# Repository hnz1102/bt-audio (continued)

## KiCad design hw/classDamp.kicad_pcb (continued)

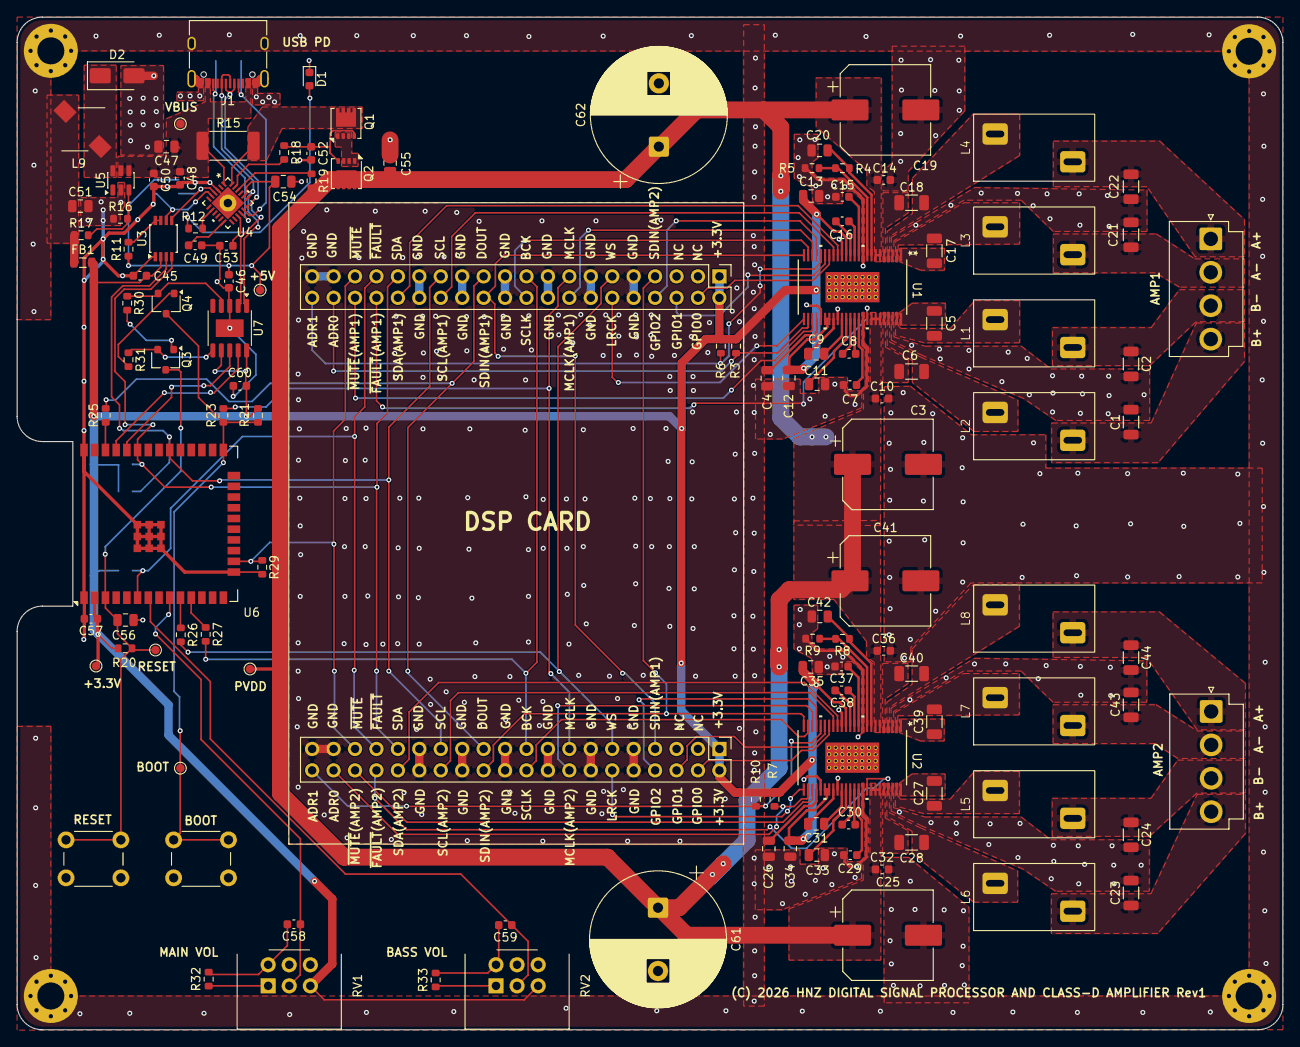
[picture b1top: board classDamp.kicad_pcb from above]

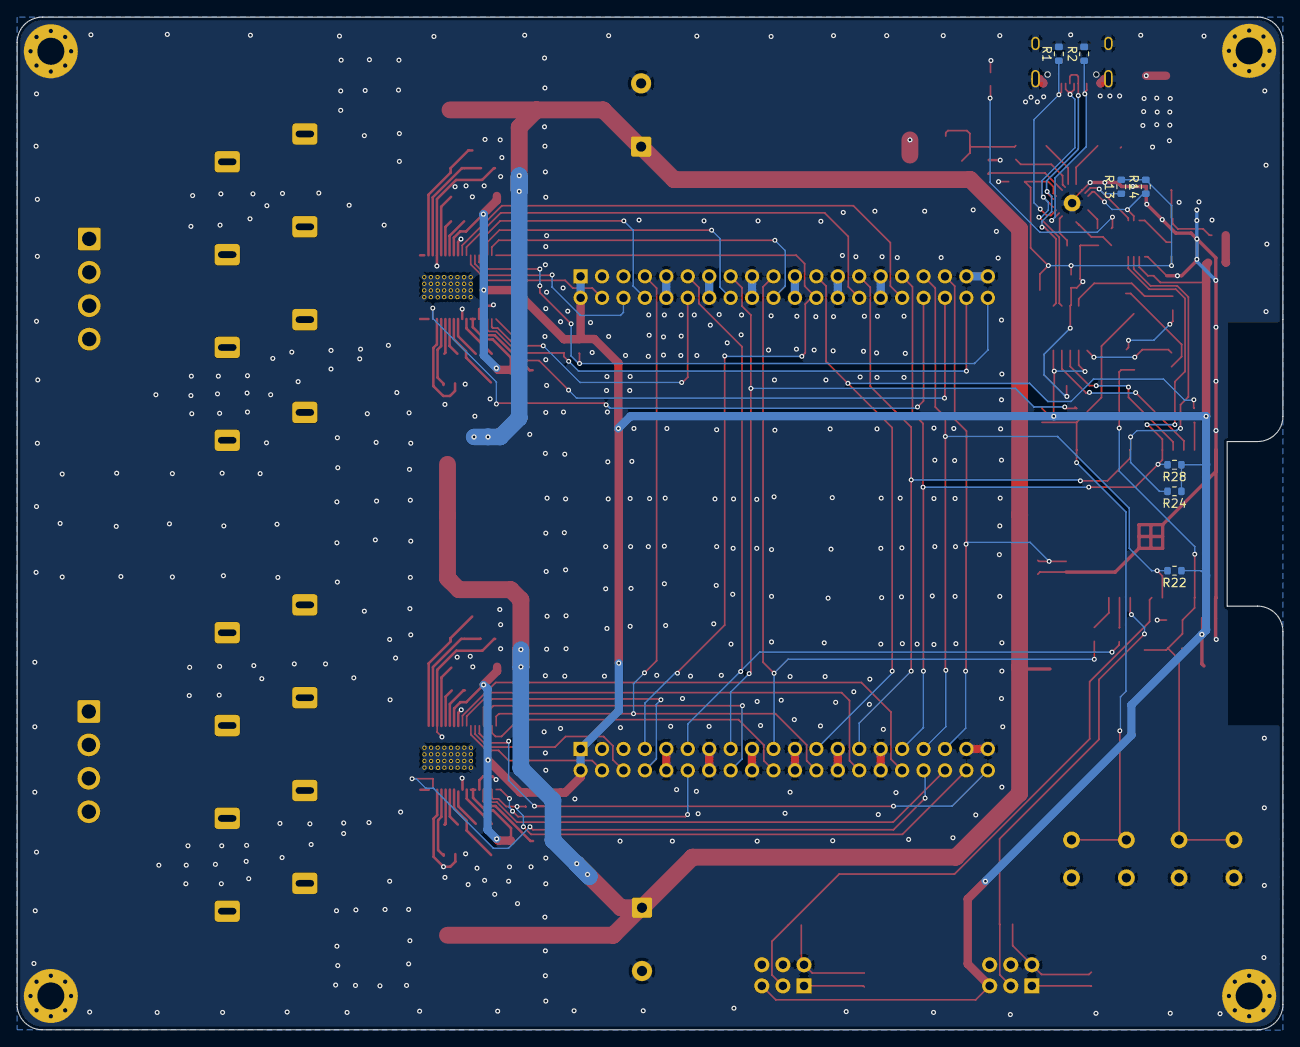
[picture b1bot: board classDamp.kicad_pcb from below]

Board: 2 copper layers, 150.0 x 120.0 mm, 137 parts (7 on the bottom side), 121 nets.

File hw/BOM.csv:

"Reference","Qty","Value","DNP","Footprint","digikey/akizuki"
"C1,C2,C21,C22,C23,C24,C43,C44","8","0.68uF","","Capacitor_SMD:C_1206_3216Metric","445-4013-1-ND"
"C3,C19,C25,C41","4","100uF/63V","","Capacitor_SMD:CP_Elec_10x12.5","63SGV100M10x10.5/112940"
"C4,C9,C11,C12,C13,C20,C26,C31,C33,C34,C35,C42,C54,C56","14","1uF","","Capacitor_SMD:C_0805_2012Metric","1276-1026-1-ND"
"C5,C6,C17,C18,C27,C28,C39,C40","8","0.22uF/50V","","Capacitor_SMD:C_1206_3216Metric","115773"
"C7,C8,C15,C16,C29,C30,C37,C38","8","2.2uF","","Capacitor_SMD:C_0603_1608Metric","1276-1040-1-ND"
"C10,C14,C32,C36,C48,C53","6","0.1uF/50V","","Capacitor_SMD:C_0603_1608Metric","311-1344-1-ND"
"C45,C46,C49,C57,C58,C59,C60","7","0.1uF","","Capacitor_SMD:C_0603_1608Metric","311-1343-1-ND"
"C47,C55","2","10uF/50V","","Capacitor_SMD:C_0805_2012Metric","490-GRM21BR61H106KE43KCT-ND"
"C50","1","2.2uF/50V","","Capacitor_SMD:C_0603_1608Metric","587-4320-1-ND"
"C51","1","47uF","","Capacitor_SMD:C_0805_2012Metric","587-4280-1-ND"
"C52","1","0.01uF/50V","","Capacitor_SMD:C_0603_1608Metric","311-1085-1-ND"
"C61,C62","2","1000uF/50V","","Capacitor_THT:CP_Radial_D16.0mm_P7.50mm","108442"
"D1","1","LED BLUE","","LED_SMD:LED_0603_1608Metric","3147-B1931NB--20C007614U1930CT-ND"
"D2","1","SK36A-LTP","","Diode_SMD:D_SMA","SK36A-LTPMSCT-ND"
"FB1","1","MH2029-601Y","","Inductor_SMD:L_0805_2012Metric","MH2029-601YCT-ND"
"H1,H2,H3,H4","4","MP","","MountingHole:MountingHole_3.2mm_M3_Pad_Via","-"
"J1","1","USB4105-GF-A","","Library:USB_C_5077CR-16-SMC2-BK-TR","2073-USB4105-GF-ACT-ND"
"J2","1","Amp1Selector","","Connector_PinHeader_2.54mm:PinHeader_2x20_P2.54mm_Vertical","100080"
"J3","1","Amp2Selector","","Connector_PinHeader_2.54mm:PinHeader_2x20_P2.54mm_Vertical","100080"
"J4","1","SPEAKER_OUT_1","","Connector_JST:JST_VH_B4P-VH_1x04_P3.96mm_Vertical","112817"
"J5","1","SPEAKER_OUT_2","","Connector_JST:JST_VH_B4P-VH_1x04_P3.96mm_Vertical","112817"
"L1,L2,L3,L4,L5,L6,L7,L8","8","10uH","","Library:Inductor_7G14C","115257"
"L9","1","22uH","","Library:L_CHPH4D19FNP","308-1313-1-ND"
"Q1,Q2","2","DMN3009LFV-7","","Package_SON:Diodes_PowerDI3333-8","31-DMN3009LFV-7CT-ND"
"Q3,Q4","2","2SC3325","","Package_TO_SOT_SMD:SC-59","100628"
"R1,R2,R17","3","5K1","","Resistor_SMD:R_0603_1608Metric","311-5.10KHRCT-ND"
"R3,R6,R7,R10,R20,R21,R22,R30,R31","9","10K","","Resistor_SMD:R_0603_1608Metric","311-10.0KHRCT-ND"
"R4,R8","2","150K","","Resistor_SMD:R_0603_1608Metric","13-RC0603FR-13150KLCT-ND"
"R5,R9","2","750K","","Resistor_SMD:R_0603_1608Metric","311-750KHRCT-ND"
"R11","1","200K","","Resistor_SMD:R_0603_1608Metric","311-200KHRCT-ND"
"R12,R32,R33","3","1K","","Resistor_SMD:R_0603_1608Metric","311-1.00KHRCT-ND"
"R13,R14,R24,R28","4","4.7K","","Resistor_SMD:R_0603_1608Metric","311-4.70KHRCT-ND"
"R15","1","5m","","Resistor_SMD:R_2512_6332Metric_Pad1.40x3.35mm_HandSolder","4506-PEWF2512D5L00Q9CT-ND "
"R16","1","3K09","","Resistor_SMD:R_0603_1608Metric","311-3.09KHRCT-ND"
"R18,R19","2","100","","Resistor_SMD:R_0603_1608Metric","311-100CRCT-ND"
"R23,R25,R26,R27","4","33","","Resistor_SMD:R_0603_1608Metric","13-RC0603JR-1333RCT-ND"
"R29","1","100K","","Resistor_SMD:R_0603_1608Metric","311-100KLDCT-ND"
"RV1,RV2","2","10K B-TYPE","","Library:Potentiometer_Alps_RK09L_Double_Horizontal","112576"
"SW1,SW2","2","PAGE/BOOT","","Button_Switch_THT:SW_PUSH_6mm_H8mm","2223-TS02-66-70-BK-160-LCR-D-ND"
"TP5","1","5V","","TestPoint:TestPoint_Pad_D1.0mm","-"
"TP6","1","VBUS_IN","","TestPoint:TestPoint_Pad_D1.0mm","-"
"TP7","1","3V3","","TestPoint:TestPoint_Pad_D1.0mm","-"
"TP8","1","VPDD","","TestPoint:TestPoint_Pad_D1.0mm","-"
"TP9","1","BOOT","","TestPoint:TestPoint_Pad_D1.0mm","-"
"TP10","1","RESET","","TestPoint:TestPoint_Pad_D1.0mm","-"
"U1,U2","2","TAS5754MDCAR","","Library:DCA48_6P4X3P6_TEX","296-40564-1-ND"
"U3","1","NVT2002DP,118","","Package_SO:TSSOP-8_3x3mm_P0.65mm","568-5121-1-ND"
"U4","1","AP33772SDKZ-13-FA01","","Library:W-QFN4040-24_Type_A1_DIO","31-AP33772SDKZ-13-FA01CT-ND"
"U5","1","NJW1933F1","","Package_TO_SOT_SMD:SOT-23-6","2129-NJW1933F1-AT-TE2-ND"
"U6","1","ESP32-WROOM-32E","","Library:ESP32-WROOM-32E","115675"
"U7","1","CH340K","","Package_SO:SSOP-10-1EP_3.9x4.9mm_P1mm_EP2.1x3.3mm","116306"

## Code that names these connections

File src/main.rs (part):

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// No packet for this long: the DMA (~43 ms) has run dry, so buffer again.
const GAP: Duration = Duration::from_millis(60);

// I2S pins for the amplifiers. MCLK (256 x fs) must be GPIO0, 1 or 3 on the ESP32.
const PIN_BCK: i32 = 26;
const PIN_WS: i32 = 25;
const PIN_DOUT: i32 = 22;
const PIN_MCLK: i32 = 0;

// I2C bus shared by both amplifiers, with external pull-ups.
const PIN_SDA: i32 = 21;
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
// SPK_MUTE of both amplifiers: high = play, low = soft mute. A 100k pull-down
// keeps them muted until the firmware drives the pin.
const PIN_MUTE: i32 = 13;
// SPK_FAULT of both amplifiers, wired together, active low (external pull-up).
const PIN_FAULT: i32 = 34;

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// need a ~30 V peak, more than PVDD, so the amplifier output clips on loud
// passages (heard as crackling, mostly on the woofer).
const AMP_GAIN_DBV: f32 = 26.427;
// Fraction of PVDD the BTL output can swing to before clipping (output stage
// drop under load).
const PVDD_SWING: f32 = 0.9;
// Extra attenuation (0.5 dB steps) applied on top of the knob so full scale
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    }
    esp!(unsafe { bt_shim_adc_add(PIN_VOL_MAIN) })?;
    esp!(unsafe { bt_shim_adc_add(PIN_VOL_WOOFER) })?;
    esp!(unsafe { bt_shim_i2s_start(DEFAULT_SAMPLE_RATE, PIN_BCK, PIN_WS, PIN_DOUT, PIN_MCLK, if SPLIT_WOOFER { 32 } else { 16 }) })?;

    // The amplifiers detect their clocks from MCLK / BCK / LRCK, so configure
    // them once the I2S clocks are running.
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    unsafe {
        // Low before the output is enabled, so the amplifiers never see a
        // high pulse.
        esp!(gpio_set_level(PIN_MUTE, 0))?;
        esp!(gpio_config(&pin(gpio_mode_t_GPIO_MODE_OUTPUT, PIN_MUTE)))?;
        esp!(gpio_config(&pin(gpio_mode_t_GPIO_MODE_INPUT, PIN_FAULT)))
    }
}

/// Drives SPK_MUTE of both amplifiers: low soft-mutes them, high plays.
fn set_amp_mute(mute: bool) -> Result<(), EspError> {
    esp!(unsafe { gpio_set_level(PIN_MUTE, if mute { 0 } else { 1 }) })
}

fn amp_write(addr: u8, reg: u8, val: u8) -> Result<(), EspError> {
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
